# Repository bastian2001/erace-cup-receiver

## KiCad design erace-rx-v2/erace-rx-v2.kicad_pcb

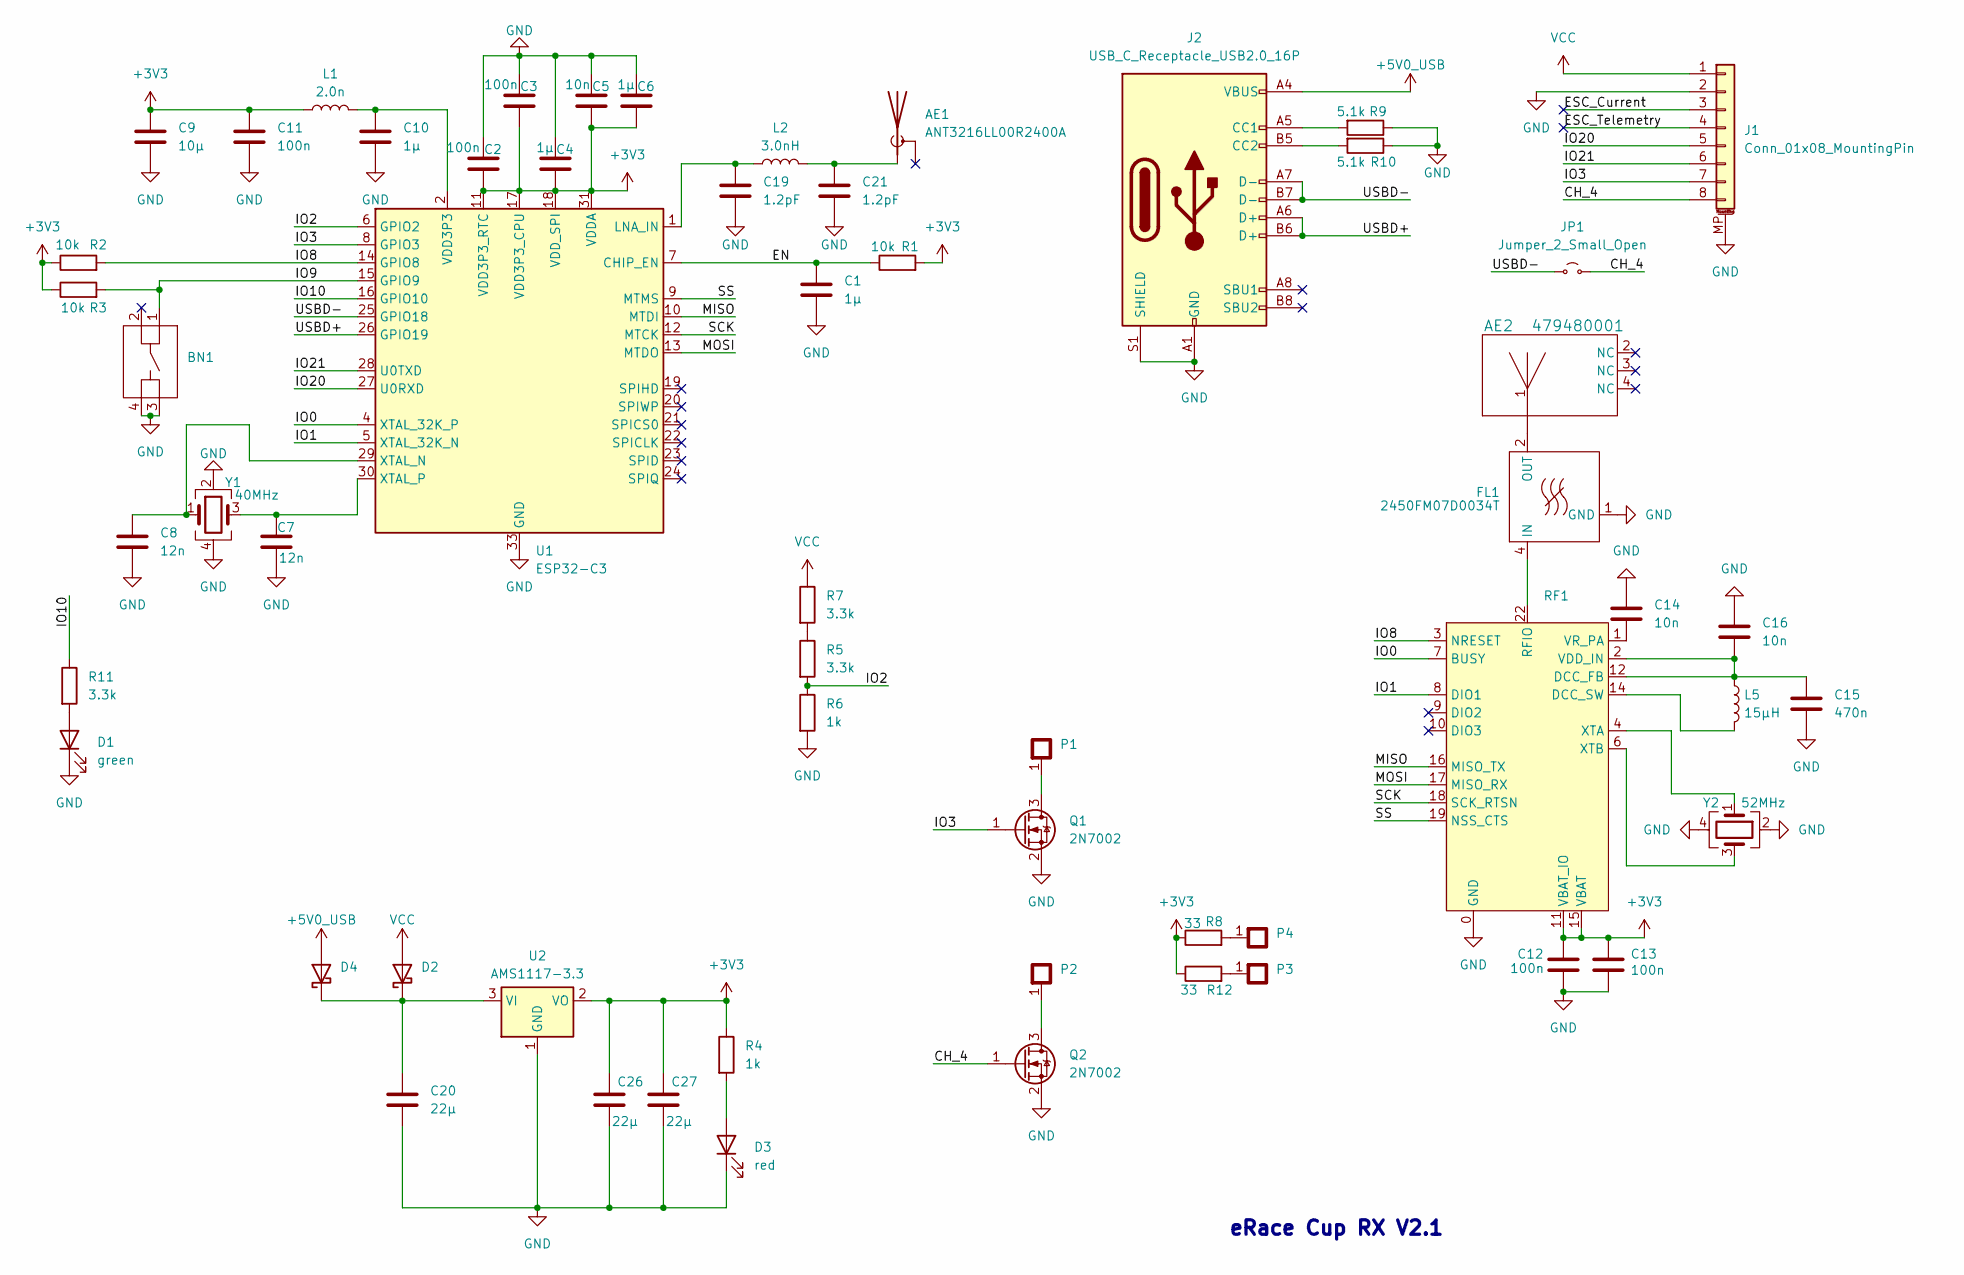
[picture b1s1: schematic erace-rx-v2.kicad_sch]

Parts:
AE1: ANT3216LL00R2400A; 1206 antenna
AE2: 479480001; ANT_47948-0001_MOL
BN1: button
C1, C4, C6, C10: 1µ; C_0402_1005Metric
C2, C3, C11, C12, C13: 100n; C_0402_1005Metric
C5, C14, C16: 10n; C_0402_1005Metric
C7, C8: 12n; C_0402_1005Metric
C9: 10µ; C_0603_1608Metric
C15: 470n; C_0603_1608Metric
C19, C21: 1.2pF; C_0402_1005Metric
C20, C26, C27: 22µ; C_0805_2012Metric
D1: green; LED_0402_1005Metric
D2, D4: D_Schottky; D_SOD-323
D3: red; LED_0402_1005Metric
FL1: 2450FM07D0034T; 0402 RF Filter
J1: Conn_01x08_MountingPin; JST_SH_SM08B-SRSS-TB_1x08-1MP_P1.00mm_Horizontal
J2: USB_C_Receptacle_USB2.0_16P; USB-C
JP1: Jumper_2_Small_Open; solder bridge
L1: 2.0n; L_0402_1005Metric
L2: 3.0nH; L_0402_1005Metric
L5: 15µH; L_0603_1608Metric
P1, P2, P3, P4: Solder Pad
Q1, Q2: 2N7002; SOT-23
R1, R2, R3: 10k; R_0402_1005Metric
R4, R6: 1k; R_0402_1005Metric
R5, R7, R11: 3.3k; R_0402_1005Metric
R8, R12: 33; R_0402_1005Metric
R9, R10: 5.1k; R_0402_1005Metric
RF1: SX128x
U1: ESP32-C3; QFN-32-1EP_5x5mm_P0.5mm_EP3.7x3.7mm
U2: AMS1117-3.3; SOT-223-3_TabPin2
Y1: 40MHz; Crystal_SMD_3225-4Pin_3.2x2.5mm
Y2: 52MHz; Crystal_SMD_3225-4Pin_3.2x2.5mm

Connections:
+3V3: C2.2, C3.2, C4.2, C5.2, C6.2, C9.1, C11.1, C12.1, C13.1, C26.1, C27.1, L1.1, R1.2, R2.1, R3.1, R4.1, R8.1, R12.1, RF1.11 (VBAT_IO), RF1.15 (VBAT), U1.11 (VDD3P3_RTC), U1.17 (VDD3P3_CPU), U1.18 (VDD_SPI), U1.31 (VDDA), U1.32 (VDDA), U2.2 (VO)
+5V0_USB: D4.2 (A), J2.A4 (VBUS), J2.A9 (VBUS), J2.B4 (VBUS), J2.B9 (VBUS)
/CH_4: J1.8, JP1.2 (B), Q2.1 (G)
/EN: C1.1, R1.1, U1.7 (CHIP_EN)
/ESC_Current: J1.3
/ESC_Telemetry: J1.4
/IO0: RF1.7 (BUSY), U1.4 (XTAL_32K_P)
/IO1: RF1.8 (DIO1), U1.5 (XTAL_32K_N)
/IO2: R5.2, R6.1, U1.6 (GPIO2)
/IO3: J1.7, Q1.1 (G), U1.8 (GPIO3)
/IO8: R2.2, RF1.3 (NRESET), U1.14 (GPIO8)
/IO9: BN1.1, R3.2, U1.15 (GPIO9)
/IO10: R11.1, U1.16 (GPIO10)
/IO20: J1.5, U1.27 (U0RXD)
/IO21: J1.6, U1.28 (U0TXD)
/MISO: RF1.16 (MISO_TX), U1.10 (MTDI)
/MOSI: RF1.17 (MISO_RX), U1.13 (MTDO)
/SCK: RF1.18 (SCK_RTSN), U1.12 (MTCK)
/SS: RF1.19 (NSS_CTS), U1.9 (MTMS)
/USBD+: J2.A6 (D+), J2.B6 (D+), U1.26 (GPIO19)
/USBD-: J2.A7 (D-), J2.B7 (D-), JP1.1 (A), U1.25 (GPIO18)
GND: BN1.3, BN1.4, C1.2, C2.1, C3.1, C4.1, C5.1, C6.1, C7.2, C8.2, C9.2, C10.2, C11.2, C12.2, C13.2, C14.1, C15.2, C16.1, C19.1, C20.2, C21.2, C26.2, C27.2, D1.1 (K), D3.1 (K), FL1.1 (GND), FL1.3 (GND), J1.2, J1.MP (MountPin), J2.A1 (GND), J2.A12 (GND), J2.B1 (GND), J2.B12 (GND), J2.S1 (SHIELD), Q1.2 (S), Q2.2 (S), R6.2, R9.1, R10.1, RF1.0 (GND), RF1.5 (GND), RF1.13 (GND), RF1.20 (GND), RF1.21 (GND), RF1.23 (GND), RF1.24 (GND), U1.33 (GND), U2.1 (GND), Y1.2, Y1.4, Y2.2, Y2.4
unnamed: AE1.1 (A), C21.1, L2.2
unnamed: D1.2 (A), R11.2
unnamed: C20.1, D2.1 (K), D4.1 (K), U2.3 (VI)
unnamed: D3.2 (A), R4.2
unnamed: FL1.4 (IN), RF1.22 (RFIO)
unnamed: AE2.1, FL1.2 (OUT)
unnamed: J2.A5 (CC1), R9.2
unnamed: J2.B5 (CC2), R10.2
unnamed: P3.1, R12.2
unnamed: P4.1, R8.2
unnamed: P1.1, Q1.3 (D)
unnamed: P2.1, Q2.3 (D)
unnamed: R5.1, R7.2
unnamed: C15.1, C16.2, L5.1, RF1.2 (VDD_IN), RF1.12 (DCC_FB)
unnamed: L5.2, RF1.14 (DCC_SW)
unnamed: C14.2, RF1.1 (VR_PA)
unnamed: RF1.4 (XTA), Y2.1
unnamed: RF1.6 (XTB), Y2.3
unnamed: C19.2, L2.1, U1.1 (LNA_IN)
unnamed: C8.1, U1.29 (XTAL_N), Y1.1
unnamed: C7.1, U1.30 (XTAL_P), Y1.3
VCC: D2.2 (A), J1.1, R7.1
VDD3P3: C10.1, L1.2, U1.2 (VDD3P3), U1.3 (VDD3P3)

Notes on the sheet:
eRace Cup RX V2.1

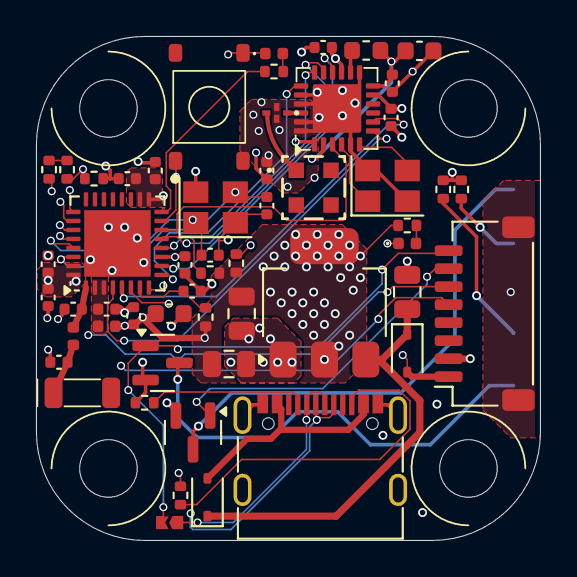
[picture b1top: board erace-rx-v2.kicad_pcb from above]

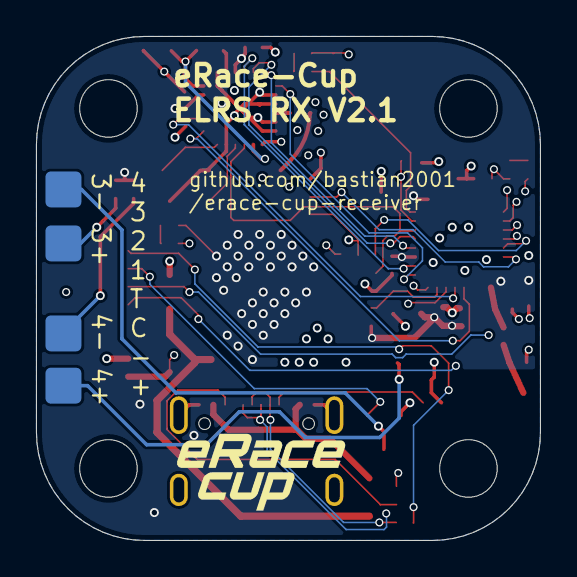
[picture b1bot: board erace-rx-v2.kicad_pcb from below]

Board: 4 copper layers, 28.0 x 28.0 mm, 58 parts (4 on the bottom side), 43 nets.

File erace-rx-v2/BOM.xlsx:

Designator | Footprint | JLCPCB Part #（optional） |  | Comment
AE1 | 1206 | C293767 |  | ANT3216LL00R2400A
AE2 | SMD | C152351 |  | 0479480001 2.4GHz Molex
BN1 | SMD | C318884 |  | TS-1187A-B-A-B
C1,C4,C6,C10 | 0402 | C52923 |  | 1uF
C15 | 0603 | C1623 |  | 470nF
C19,C21 | 0402 | C72135 |  | 1.2pF
C2,C3,C11,C12,C13 | 0402 | C307331 |  | 100 nF
C20,C26,C27 | 0805 | C45783 |  | 22uF
C5,C14,C16 | 0402 | C15195 |  | 10nF
C7,C8 | 0402 | C1547 |  | 12pF
C9 | 0603 | C19702 |  | 10uF
D1 | 0402 | C965794 |  | LED green
D2,D4 | SOD-323 | C191023 |  | 1N5819WS
FL1 | 0402-4P | C6054595 |  | 2.4GHz Filter RF
J1 | SMD,P=1mm | C5340778 |  | 1.0mm-8P-WT
J2 | SMD | C393939 |  | TYPE-C16PIN
L1 | 0402 | C880712 |  | 2.0nH
L2 | 0402 | C19898 |  | 3.0nH
L5 | 0603 | C57838 |  | 15µH
P1,P2,P3,P4 |  |  | do not populate | Solder Pad
Q1,Q2 | SOT-23 | C8545 |  | 2N7002 MOSFET Jiangsu
R1,R2,R3 | 0402 | C25744 |  | 10k
R13 |  |  | do not populate | 0 Ohm
R4,R6 | 0402 | C11702 |  | 1k
R5,R7,R11 | 0402 | C25890 |  | 3.3k
R8,R12 | 0402 | C25105 |  | 33 Ohm
R9,R10 | 0402 | C25905 |  | 5.1k
RF1 | QFN-24-EP(4x4) | C2151551 |  | SX1281IMLTRT
U1 | QFN-32-EP(5x5) | C2858491 |  | ESP32-C3FH4
U2 | SOT-223 | C6186 |  | AMS1117-3.3
Y1 | SMD3225-4P | C331597 |  | 40MHz Crystal
Y2 | SMD3225-4P | C7294606 |  | 52MHz Crystal
D3 | 0402 | C25503345 |  | LED red

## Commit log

2024-07-09 started first version
2024-07-10 move one folder up
2024-07-10 v2 layout
2024-07-12 0 DRC violations :tada:
2024-07-13 corrected XTAL, updated for JLC stock
2024-07-13 remove lockfile
2024-07-13 gitignore lck files
2024-08-12 adjusted for Johanson filter, moved power LED
2024-11-29 V2.1 as ordered
